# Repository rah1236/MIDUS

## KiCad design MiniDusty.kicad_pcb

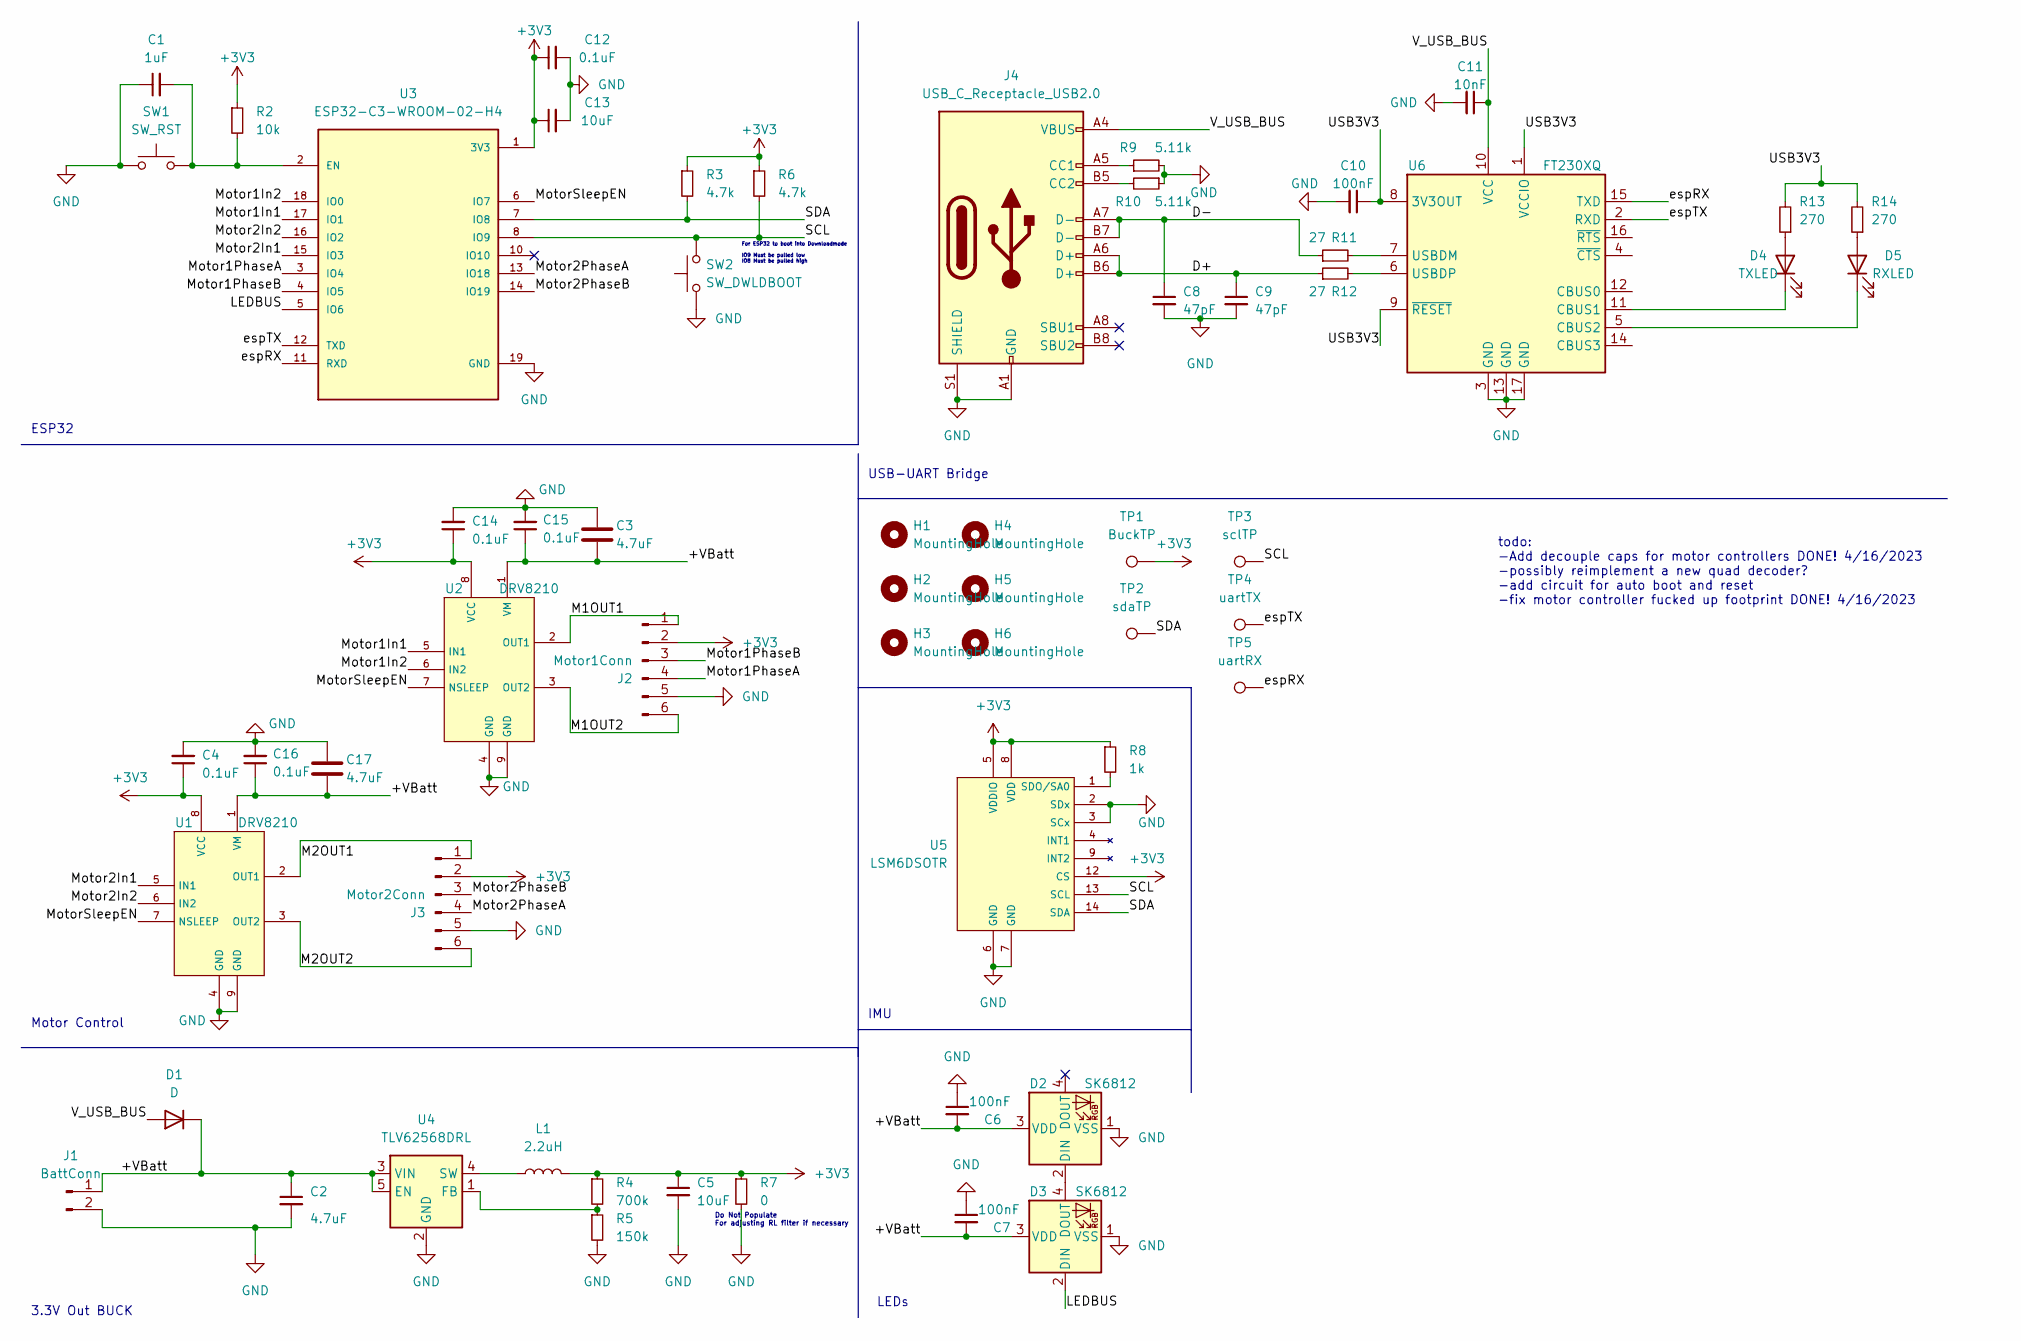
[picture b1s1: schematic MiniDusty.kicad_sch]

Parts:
C1: 1uF; C_0603_1608Metric
C2: 4.7uF; C_0603_1608Metric
C3, C17: 4.7uF; CP_Radial_D5.0mm_P2.50mm
C4, C12, C14, C15, C16: 0.1uF; C_0603_1608Metric
C5, C13: 10uF; C_0603_1608Metric
C6, C7, C10: 100nF; C_0603_1608Metric
C8, C9: 47pF; C_0603_1608Metric
C11: 10nF; C_0603_1608Metric
D1: D; D_0603_1608Metric
D2, D3: SK6812; LED_SK6812_PLCC4_5.0x5.0mm_P3.2mm
D4: TXLED; LED_0603_1608Metric
D5: RXLED; LED_0603_1608Metric
H1, H2, H3, H4, H5, H6: MountingHole; MountingHole_3.2mm_M3
J1: BattConn; PinHeader_1x02_P2.54mm_Vertical
J2: Motor1Conn; PinSocket_1x06_P2.54mm_Vertical
J3: Motor2Conn; PinSocket_1x06_P2.54mm_Vertical
J4: USB_C_Receptacle_USB2.0; USB_C_Receptacle_GCT_USB4115-03-C
L1: 2.2uH; L_Taiyo-Yuden_NR-30xx
R2: 10k; R_0603_1608Metric
R3, R6: 4.7k; R_0603_1608Metric
R4: 700k; R_0603_1608Metric
R5: 150k; R_0603_1608Metric
R7: 0; C_0603_1608Metric
R8: 1k; R_0603_1608Metric
R9, R10: 5.11k; R_0603_1608Metric
R11, R12: 27; R_0603_1608Metric
R13, R14: 270; R_0603_1608Metric
SW1: SW_RST; SW_SPST_B3U-1000P
SW2: SW_DWLDBOOT; SW_SPST_B3U-1000P
TP1: BuckTP; TestPoint_Pad_1.5x1.5mm
TP2: sdaTP; TestPoint_Pad_1.5x1.5mm
TP3: sclTP; TestPoint_Pad_1.5x1.5mm
TP4: uartTX; TestPoint_Pad_1.5x1.5mm
TP5: uartRX; TestPoint_Pad_1.5x1.5mm
U1, U2: DRV8210; WSON-8-1EP_2x2mm_P0.5mm_EP0.9x1.6mm_ThermalVias
U3: ESP32-C3-WROOM-02-H4; ESP-WROOM-02
U4: TLV62568DRL; SOT-563
U5: LSM6DSOTR; LGA-14_3x2.5mm_P0.5mm_LayoutBorder3x4y
U6: FT230XQ; QFN-16-1EP_4x4mm_P0.65mm_EP2.1x2.1mm

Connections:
+3V3: C4.1, C5.1, C12.1, C13.1, C14.1, J2.2, J3.2, L1.2, R2.1, R3.1, R4.1, R6.1, R7.1, R8.1, TP1.1, U1.8 (VCC), U2.8 (VCC), U3.1 (3V3), U5.5 (VDDIO), U5.8 (VDD), U5.12 (CS)
/+VBatt: C2.1, C3.1, C6.2, C7.2, C15.1, C16.1, C17.1, D1.1 (K), D2.3 (VDD), D3.3 (VDD), J1.1, U1.1 (VM), U2.1 (VM), U4.3 (VIN), U4.5 (EN)
/D+: C9.1, J4.A6 (D+), J4.B6 (D+), R12.1
/D-: C8.1, J4.A7 (D-), J4.B7 (D-), R11.1
/LEDBUS: D3.2 (DIN), U3.5 (IO6)
/M1OUT1: J2.1, U2.2 (OUT1)
/M1OUT2: J2.6, U2.3 (OUT2)
/M2OUT1: J3.1, U1.2 (OUT1)
/M2OUT2: J3.6, U1.3 (OUT2)
/Motor1In1: U2.5 (IN1), U3.17 (IO1)
/Motor1In2: U2.6 (IN2), U3.18 (IO0)
/Motor1PhaseA: J2.4, U3.3 (IO4)
/Motor1PhaseB: J2.3, U3.4 (IO5)
/Motor2In1: U1.5 (IN1), U3.15 (IO3)
/Motor2In2: U1.6 (IN2), U3.16 (IO2)
/Motor2PhaseA: J3.4, U3.13 (IO18)
/Motor2PhaseB: J3.3, U3.14 (IO19)
/MotorSleepEN: U1.7 (NSLEEP), U2.7 (NSLEEP), U3.6 (IO7)
/SCL: R6.2, SW2.2, TP3.1, U3.8 (IO9), U5.13 (SCL)
/SDA: R3.2, TP2.1, U3.7 (IO8), U5.14 (SDA)
/USB3V3: C10.1, R13.2, R14.2, U6.1 (VCCIO), U6.8 (3V3OUT), U6.9 (~RESET)
/V_USB_BUS: C11.1, D1.2 (A), J4.A4 (VBUS), J4.A9 (VBUS), J4.B4 (VBUS), J4.B9 (VBUS), U6.10 (VCC)
/espRX: TP5.1, U3.11 (RXD), U6.15 (TXD)
/espTX: TP4.1, U3.12 (TXD), U6.2 (RXD)
GND: C1.1, C2.2, C3.2, C4.2, C5.2, C6.1, C7.1, C8.2, C9.2, C10.2, C11.2, C12.2, C13.2, C14.2, C15.2, C16.2, C17.2, D2.1 (VSS), D3.1 (VSS), J1.2, J2.5, J3.5, J4.A1 (GND), J4.A12 (GND), J4.B1 (GND), J4.B12 (GND), J4.S1 (SHIELD), R5.2, R7.2, R9.2, R10.1, SW1.1, SW2.1, U1.4 (GND), U1.9 (GND), U2.4 (GND), U2.9 (GND), U3.19 (GND), U4.2 (GND), U5.2 (SDx), U5.3 (SCx), U5.6 (GND), U5.7 (GND), U6.3 (GND), U6.13 (GND), U6.17 (GND)
unnamed: D2.2 (DIN), D3.4 (DOUT)
unnamed: D4.2 (A), R13.1
unnamed: D4.1 (K), U6.11 (CBUS1)
unnamed: D5.2 (A), R14.1
unnamed: D5.1 (K), U6.5 (CBUS2)
unnamed: J4.A5 (CC1), R9.1
unnamed: J4.B5 (CC2), R10.2
unnamed: C1.2, R2.2, SW1.2, U3.2 (EN)
unnamed: R4.2, R5.1, U4.1 (FB)
unnamed: L1.1, U4.4 (SW)
unnamed: R8.2, U5.1 (SDO/SA0)
unnamed: R11.2, U6.7 (USBDM)
unnamed: R12.2, U6.6 (USBDP)

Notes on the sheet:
USB-UART Bridge
LEDs
IMU
3.3V Out BUCK
For ESP32 to boot into Downloadmode IO9 Must be pulled low IO8 Must be pulled high
Do Not Populate For adjusting RL filter if necessary
Motor Control
todo: -Add decouple caps for motor controllers DONE! 4/16/2023 -possibly reimplement a new quad decoder? -add circuit for auto boot and reset -fix motor controller fucked up footprint DONE! 4/16/2023
ESP32

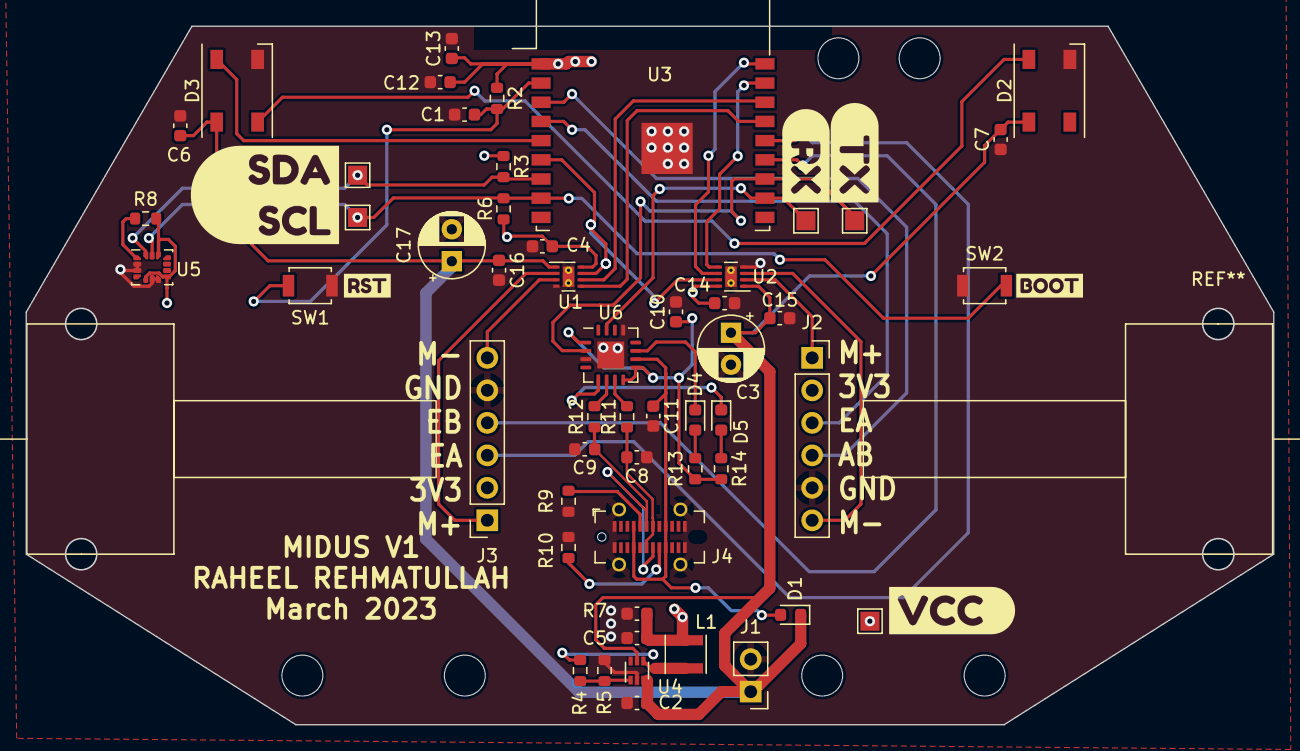
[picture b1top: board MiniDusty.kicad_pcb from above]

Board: 4 copper layers, 97.5 x 54.6 mm, 65 parts (0 on the bottom side), 38 nets.

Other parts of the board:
kibuzzard-640F5FD6: G***; kibuzzard-640F5FD6
kibuzzard-640F60AF: G***; kibuzzard-640F60AF
kibuzzard-640F60C6: G***; kibuzzard-640F60C6
kibuzzard-640F6059: G***; kibuzzard-640F6059
kibuzzard-640F6063: G***; kibuzzard-640F6063
kibuzzard-640F6079: G***; kibuzzard-640F6079

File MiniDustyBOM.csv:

"Id";"Designator";"Package";"Quantity";"Designation";"Supplier and ref";
1;"U3";"ESP-WROOM-02";1;"ESP32-C3-WROOM-02-H4";;;
2;"C13,C5";"C_0603_1608Metric";2;"10uF";;;
3;"C12";"C_0603_1608Metric";1;"0.1uF";;;
4;"REF**,REF**";"n20Motor";2;"n20Motor";;;
5;"C10,C7,C6";"C_0603_1608Metric";3;"100nF";;;
6;"D4";"LED_0603_1608Metric";1;"TXLED";;;
7;"D5";"LED_0603_1608Metric";1;"RXLED";;;
8;"L1";"L_Taiyo-Yuden_NR-30xx";1;"2.2uH";;;
9;"J3";"PinSocket_1x06_P2.54mm_Vertical";1;"Motor2Conn";;;
10;"C11";"C_0603_1608Metric";1;"10nF";;;
11;"U1,U2";"WSON-8-1EP_2x2mm_P0.5mm_EP0.9x1.6mm_ThermalVias";2;"DRV8220DSG";;;
12;"SW1";"SW_Push_1P1T_NO_CK_KSC6xxJ";1;"SW_RST";;;
13;"R4";"R_0603_1608Metric";1;"700k";;;
14;"R10,R9";"R_0603_1608Metric";2;"5.11k";;;
15;"R2";"R_0603_1608Metric";1;"10k";;;
16;"J4";"USB_C_Receptacle_GCT_USB4115-03-C";1;"USB_C_Receptacle_USB2.0";;;
17;"C3,C4";"CP_Radial_D5.0mm_P2.50mm";2;"4.7uF";;;
18;"R13,R14";"R_0603_1608Metric";2;"270";;;
19;"J1";"PinHeader_1x02_P2.54mm_Vertical";1;"BattConn";;;
20;"R8";"R_0603_1608Metric";1;"1k";;;
21;"R5";"R_0603_1608Metric";1;"150k";;;
22;"U5";"LGA-14_3x2.5mm_P0.5mm_LayoutBorder3x4y";1;"LSM6DSOTR";;;
23;"D2,D3";"LED_SK6812_PLCC4_5.0x5.0mm_P3.2mm";2;"SK6812";;;
24;"U6";"QFN-16-1EP_4x4mm_P0.65mm_EP2.1x2.1mm";1;"FT230XQ";;;
25;"R11,R12";"R_0603_1608Metric";2;"27";;;
26;"SW2";"SW_Push_1P1T_NO_CK_KSC6xxJ";1;"SW_DWLDBOOT";;;
27;"R3,R6";"R_0603_1608Metric";2;"4.7k";;;
28;"TP4";"TestPoint_Pad_1.5x1.5mm";1;"uartTX";;;
29;"C1";"C_0603_1608Metric";1;"1uF";;;
30;"C9,C8";"C_0603_1608Metric";2;"47pF";;;
31;"C2";"C_0603_1608Metric";1;"4.7uF";;;
32;"TP1";"TestPoint_Pad_1.5x1.5mm";1;"BuckTP";;;
33;"TP5";"TestPoint_Pad_1.5x1.5mm";1;"uartRX";;;
34;"D1";"D_0603_1608Metric";1;"D";;;
35;"U4";"SOT-563";1;"TLV62568DRL";;;
36;"TP3";"TestPoint_Pad_1.5x1.5mm";1;"sclTP";;;
37;"R7";"C_0603_1608Metric";1;"0";;;
38;"J2";"PinSocket_1x06_P2.54mm_Vertical";1;"Motor1Conn";;;
39;"TP2";"TestPoint_Pad_1.5x1.5mm";1;"sdaTP";;;

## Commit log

2023-06-29 init
